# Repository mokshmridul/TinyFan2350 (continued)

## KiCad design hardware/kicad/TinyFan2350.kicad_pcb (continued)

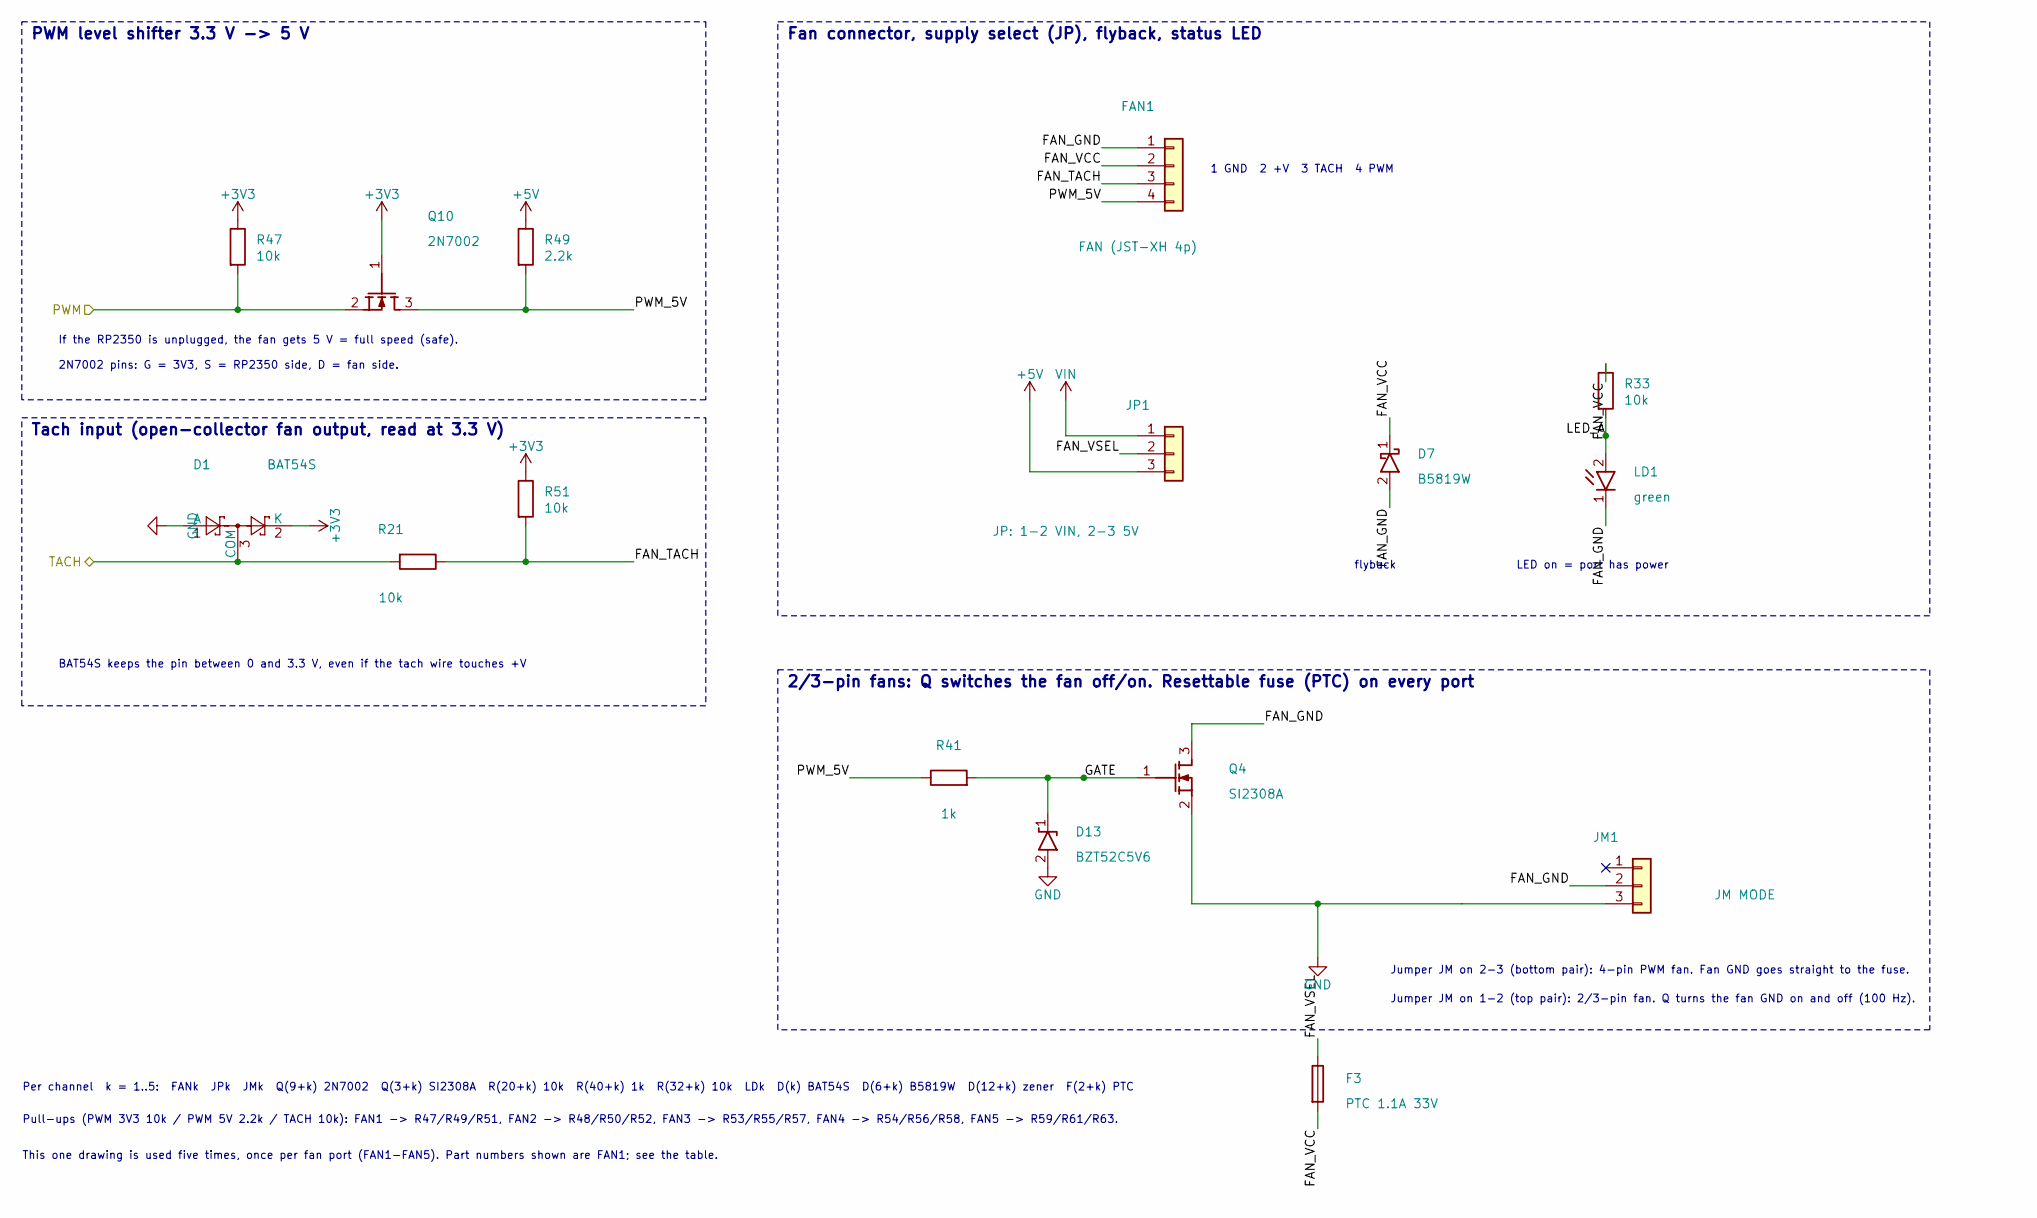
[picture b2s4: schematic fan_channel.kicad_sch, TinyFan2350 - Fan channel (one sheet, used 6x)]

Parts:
D1: BAT54S; SOT-23; MPN BAT54S-7-F; LCSC C83574
D7: B5819W; D_SOD-123; MPN B5819W; LCSC C8598
D13: BZT52C5V6; D_SOD-123; MPN BZT52C5V6; LCSC C2119
F3: PTC 1.1A 33V; Fuse_1812_4532Metric; MPN 1812L110/33GR; LCSC C7542972
FAN1: FAN (JST-XH 4p); JST_XH_B4B-XH-A_1x04_P2.50mm_Vertical; MPN B4B-XH-A(LF)(SN); LCSC C144395
JM1: JM MODE; PinHeader_1x03_P2.54mm_Vertical_TightCY; MPN 2.54-1*3P; LCSC C49257
JP1: JP: 1-2 VIN, 2-3 5V; PinHeader_1x03_P2.54mm_Vertical_TightCY; MPN 2.54-1*3P; LCSC C49257
LD1: green; LED_0805_2012Metric; MPN KT-0805G; LCSC C2297
Q4: SI2308A; SOT-23; MPN SI2308A; LCSC C347491
Q10: 2N7002; SOT-23; MPN 2N7002; LCSC C8545
R21, R33, R47, R51: 10k; R_0805_2012Metric; MPN 0805W8F1002T5E; LCSC C17414
R41: 1k; R_0805_2012Metric; MPN 0805W8F1001T5E; LCSC C17513
R49: 2.2k; R_0805_2012Metric; MPN 0805W8F2201T5E; LCSC C17520

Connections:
+3V3: D1.2 (K), Q10.1 (G), R47.1, R51.1; also elsewhere on the board
+5V: JP1.3, R49.1; also elsewhere on the board
/FAN1/FAN_GND: D7.2 (A), FAN1.1, JM1.2, LD1.1 (K), Q4.3 (D)
/FAN1/FAN_TACH: FAN1.3, R21.1, R51.2
/FAN1/FAN_VCC: D7.1 (K), F3.2, FAN1.2, R33.1
/FAN1/FAN_VSEL: F3.1, JP1.2
/FAN1/GATE: D13.1 (K), Q4.1 (G), R41.2
/FAN1/LED_A: LD1.2 (A), R33.2
/FAN1/PWM_5V: FAN1.4, Q10.3 (D), R41.1, R49.2
/FAN1_PWM: Q10.2 (S), R47.2; also elsewhere on the board
/FAN1_TACH_IO: D1.3 (COM), R21.2; also elsewhere on the board
GND: D1.1 (A), D13.2 (A), JM1.3, Q4.2 (S); also elsewhere on the board
VIN: JP1.1; also elsewhere on the board

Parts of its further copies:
D2, D3, D4, D5: BAT54S; SOT-23; MPN BAT54S-7-F; LCSC C83574
D8, D9, D10, D11: B5819W; D_SOD-123; MPN B5819W; LCSC C8598
D14, D15, D16, D17: BZT52C5V6; D_SOD-123; MPN BZT52C5V6; LCSC C2119
F4, F5, F6, F7: PTC 1.1A 33V; Fuse_1812_4532Metric; MPN 1812L110/33GR; LCSC C7542972
FAN2, FAN3, FAN4, FAN5: FAN (JST-XH 4p); JST_XH_B4B-XH-A_1x04_P2.50mm_Vertical; MPN B4B-XH-A(LF)(SN); LCSC C144395
JM2, JM3, JM4, JM5: JM MODE; PinHeader_1x03_P2.54mm_Vertical_TightCY; MPN 2.54-1*3P; LCSC C49257
JP2, JP3, JP4, JP5: JP: 1-2 VIN, 2-3 5V; PinHeader_1x03_P2.54mm_Vertical_TightCY; MPN 2.54-1*3P; LCSC C49257
LD2, LD3, LD4, LD5: green; LED_0805_2012Metric; MPN KT-0805G; LCSC C2297
Q5, Q6, Q7, Q8: SI2308A; SOT-23; MPN SI2308A; LCSC C347491
Q11, Q12, Q13, Q14: 2N7002; SOT-23; MPN 2N7002; LCSC C8545
R22, R23, R24, R25, R34, R35, R36, R37, R48, R52, R53, R54, R57, R58, R59, R63: 10k; R_0805_2012Metric; MPN 0805W8F1002T5E; LCSC C17414
R42, R43, R44, R45: 1k; R_0805_2012Metric; MPN 0805W8F1001T5E; LCSC C17513
R50, R55, R56, R61: 2.2k; R_0805_2012Metric; MPN 0805W8F2201T5E; LCSC C17520

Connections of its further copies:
+3V3: D2.2 (K), D3.2 (K), D4.2 (K), D5.2 (K), Q11.1 (G), Q12.1 (G), Q13.1 (G), Q14.1 (G), R48.1, R52.1, R53.1, R54.1, R57.1, R58.1, R59.1, R63.1; also elsewhere on the board
+5V: JP2.3, JP3.3, JP4.3, JP5.3, R50.1, R55.1, R56.1, R61.1; also elsewhere on the board
/FAN2/FAN_GND: D8.2 (A), FAN2.1, JM2.2, LD2.1 (K), Q5.3 (D)
/FAN2/FAN_TACH: FAN2.3, R22.1, R52.2
/FAN2/FAN_VCC: D8.1 (K), F4.2, FAN2.2, R34.1
/FAN2/FAN_VSEL: F4.1, JP2.2
/FAN2/GATE: D14.1 (K), Q5.1 (G), R42.2
/FAN2/LED_A: LD2.2 (A), R34.2
/FAN2/PWM_5V: FAN2.4, Q11.3 (D), R42.1, R50.2
/FAN2_PWM: Q11.2 (S), R48.2; also elsewhere on the board
/FAN2_TACH_IO: D2.3 (COM), R22.2; also elsewhere on the board
/FAN3/FAN_GND: D9.2 (A), FAN3.1, JM3.2, LD3.1 (K), Q6.3 (D)
/FAN3/FAN_TACH: FAN3.3, R23.1, R57.2
/FAN3/FAN_VCC: D9.1 (K), F5.2, FAN3.2, R35.1
/FAN3/FAN_VSEL: F5.1, JP3.2
/FAN3/GATE: D15.1 (K), Q6.1 (G), R43.2
/FAN3/LED_A: LD3.2 (A), R35.2
/FAN3/PWM_5V: FAN3.4, Q12.3 (D), R43.1, R55.2
/FAN3_PWM: Q12.2 (S), R53.2; also elsewhere on the board
/FAN3_TACH_IO: D3.3 (COM), R23.2; also elsewhere on the board
/FAN4/FAN_GND: D10.2 (A), FAN4.1, JM4.2, LD4.1 (K), Q7.3 (D)
/FAN4/FAN_TACH: FAN4.3, R24.1, R58.2
/FAN4/FAN_VCC: D10.1 (K), F6.2, FAN4.2, R36.1
/FAN4/FAN_VSEL: F6.1, JP4.2
/FAN4/GATE: D16.1 (K), Q7.1 (G), R44.2
/FAN4/LED_A: LD4.2 (A), R36.2
/FAN4/PWM_5V: FAN4.4, Q13.3 (D), R44.1, R56.2
/FAN4_PWM: Q13.2 (S), R54.2; also elsewhere on the board
/FAN4_TACH_IO: D4.3 (COM), R24.2; also elsewhere on the board
/FAN5/FAN_GND: D11.2 (A), FAN5.1, JM5.2, LD5.1 (K), Q8.3 (D)
/FAN5/FAN_TACH: FAN5.3, R25.1, R63.2
/FAN5/FAN_VCC: D11.1 (K), F7.2, FAN5.2, R37.1
/FAN5/FAN_VSEL: F7.1, JP5.2
/FAN5/GATE: D17.1 (K), Q8.1 (G), R45.2
/FAN5/LED_A: LD5.2 (A), R37.2
/FAN5/PWM_5V: FAN5.4, Q14.3 (D), R45.1, R61.2
/FAN5_PWM: Q14.2 (S), R59.2; also elsewhere on the board
/FAN5_TACH_IO: D5.3 (COM), R25.2; also elsewhere on the board
GND: D2.1 (A), D3.1 (A), D4.1 (A), D5.1 (A), D14.2 (A), D15.2 (A), D16.2 (A), D17.2 (A), JM2.3, JM3.3, JM4.3, JM5.3, Q5.2 (S), Q6.2 (S), Q7.2 (S), Q8.2 (S); also elsewhere on the board
VIN: JP2.1, JP3.1, JP4.1, JP5.1; also elsewhere on the board

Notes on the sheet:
This one drawing is used five times, once per fan port (FAN1-FAN5). Part numbers shown are FAN1; see the table.
PWM level shifter 3.3 V -> 5 V
If the RP2350 is unplugged, the fan gets 5 V = full speed (safe).
2N7002 pins: G = 3V3, S = RP2350 side, D = fan side.
Tach input (open-collector fan output, read at 3.3 V)
BAT54S keeps the pin between 0 and 3.3 V, even if the tach wire touches +V
Fan connector, supply select (JP), flyback, status LED
1 GND 2 +V 3 TACH 4 PWM
flyback
LED on = port has power
2/3-pin fans: Q switches the fan off/on. Resettable fuse (PTC) on every port
Jumper JM on 2-3 (bottom pair): 4-pin PWM fan. Fan GND goes straight to the fuse.
Jumper JM on 1-2 (top pair): 2/3-pin fan. Q turns the fan GND on and off (100 Hz).
Per channel k = 1..5: FANk JPk JMk Q(9+k) 2N7002 Q(3+k) SI2308A R(20+k) 10k R(40+k) 1k R(32+k) 10k LDk D(k) BAT54S D(6+k) B5819W D(12+k) zener F(2+k) PTC
Pull-ups (PWM 3V3 10k / PWM 5V 2.2k / TACH 10k): FAN1 -> R47/R49/R51, FAN2 -> R48/R50/R52, FAN3 -> R53/R55/R57, FAN4 -> R54/R56/R58, FAN5 -> R59/R61/R63.

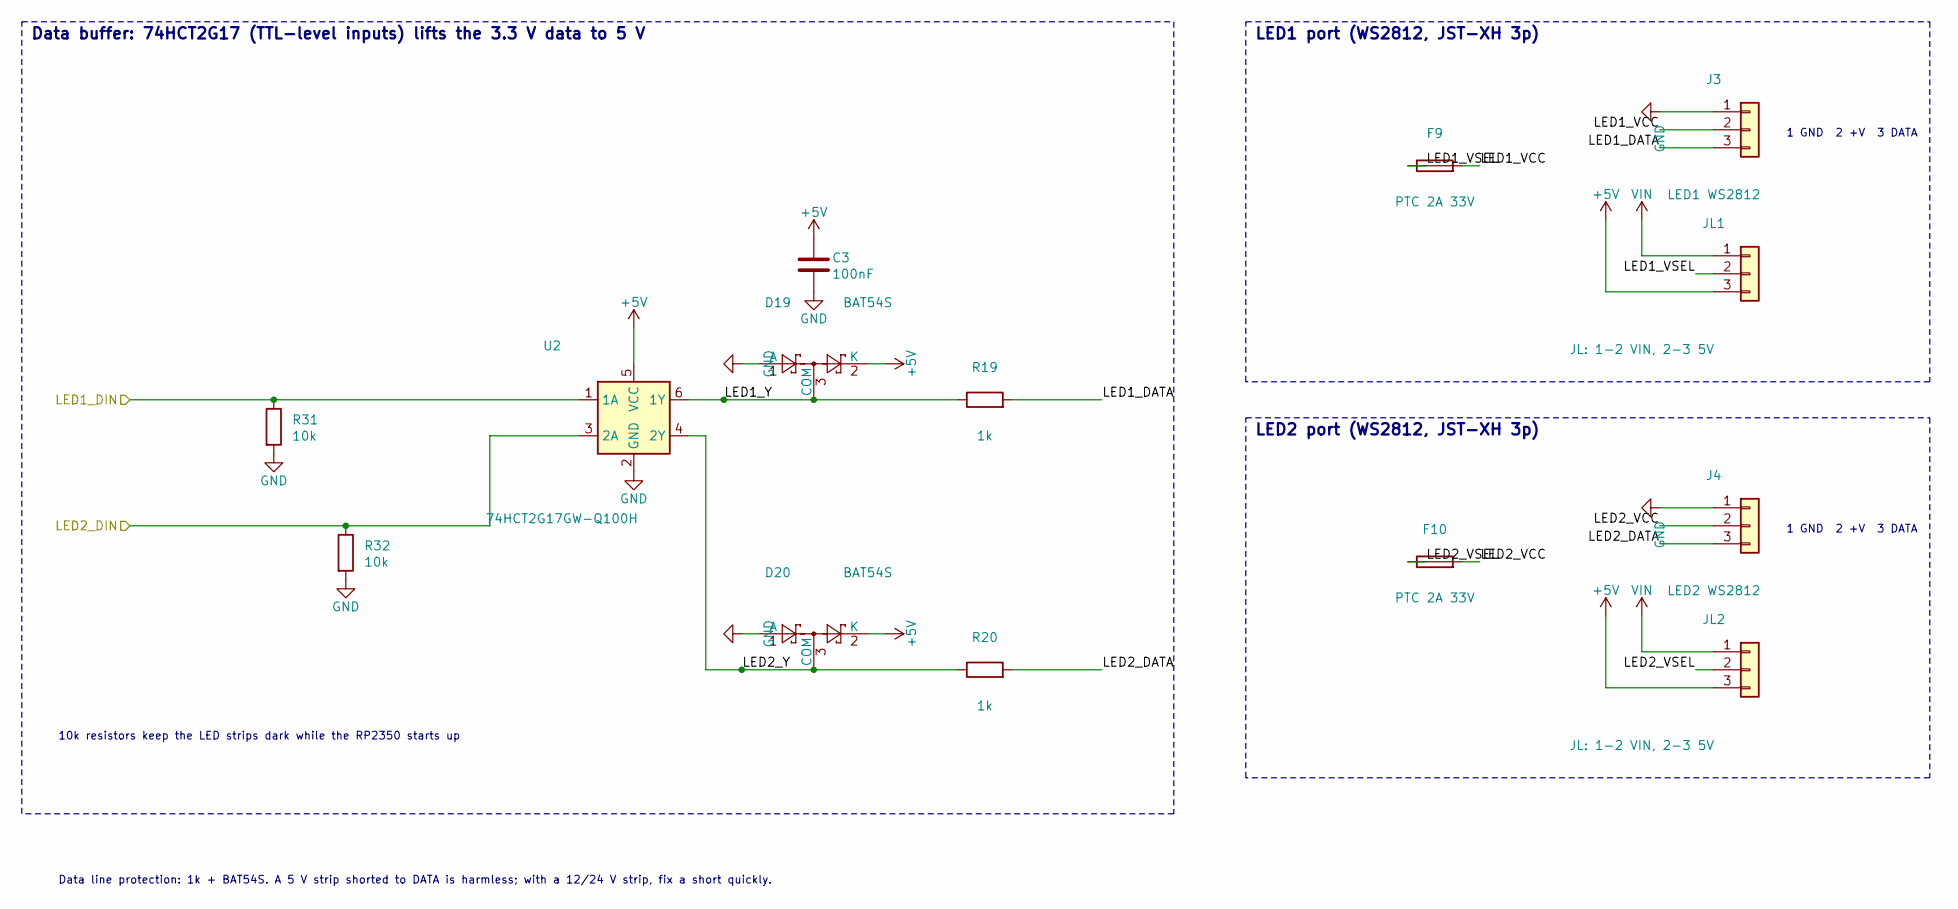
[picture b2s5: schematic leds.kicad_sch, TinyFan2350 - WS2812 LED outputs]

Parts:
C3: 100nF; C_0805_2012Metric; MPN CC0805KRX7R9BB104; LCSC C49678
D19, D20: BAT54S; SOT-23; MPN BAT54S-7-F; LCSC C83574
F9, F10: PTC 2A 33V; Fuse_1812_4532Metric; MPN 1812L200/33GR; LCSC C18198343
J3: LED1 WS2812; JST_XH_B3B-XH-A_1x03_P2.50mm_Vertical; MPN B3B-XH-A(LF)(SN); LCSC C144394
J4: LED2 WS2812; JST_XH_B3B-XH-A_1x03_P2.50mm_Vertical; MPN B3B-XH-A(LF)(SN); LCSC C144394
JL1, JL2: JL: 1-2 VIN, 2-3 5V; PinHeader_1x03_P2.54mm_Vertical_TightCY; MPN 2.54-1*3P; LCSC C49257
R19, R20: 1k; R_1206_3216Metric; MPN 1206W4F1001T5E; LCSC C4410
R31, R32: 10k; R_0805_2012Metric; MPN 0805W8F1002T5E; LCSC C17414
U2: 74HCT2G17GW-Q100H; SOT-363_SC-70-6; MPN 74HCT2G17GW-Q100H; LCSC C547569

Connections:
+5V: C3.1, D19.2 (K), D20.2 (K), JL1.3, JL2.3, U2.5 (VCC); also elsewhere on the board
/LED1_DIN: R31.1, U2.1 (1A); also elsewhere on the board
/LED2_DIN: R32.1, U2.3 (2A); also elsewhere on the board
/LEDs/LED1_DATA: J3.3, R19.2
/LEDs/LED1_VCC: F9.2, J3.2
/LEDs/LED1_VSEL: F9.1, JL1.2
/LEDs/LED1_Y: D19.3 (COM), R19.1, U2.6 (1Y)
/LEDs/LED2_DATA: J4.3, R20.2
/LEDs/LED2_VCC: F10.2, J4.2
/LEDs/LED2_VSEL: F10.1, JL2.2
/LEDs/LED2_Y: D20.3 (COM), R20.1, U2.4 (2Y)
GND: C3.2, D19.1 (A), D20.1 (A), J3.1, J4.1, R31.2, R32.2, U2.2 (GND); also elsewhere on the board
VIN: JL1.1, JL2.1; also elsewhere on the board

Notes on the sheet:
Data buffer: 74HCT2G17 (TTL-level inputs) lifts the 3.3 V data to 5 V
10k resistors keep the LED strips dark while the RP2350 starts up
LED1 port (WS2812, JST-XH 3p)
1 GND 2 +V 3 DATA
LED2 port (WS2812, JST-XH 3p)
Data line protection: 1k + BAT54S. A 5 V strip shorted to DATA is harmless; with a 12/24 V strip, fix a short quickly.

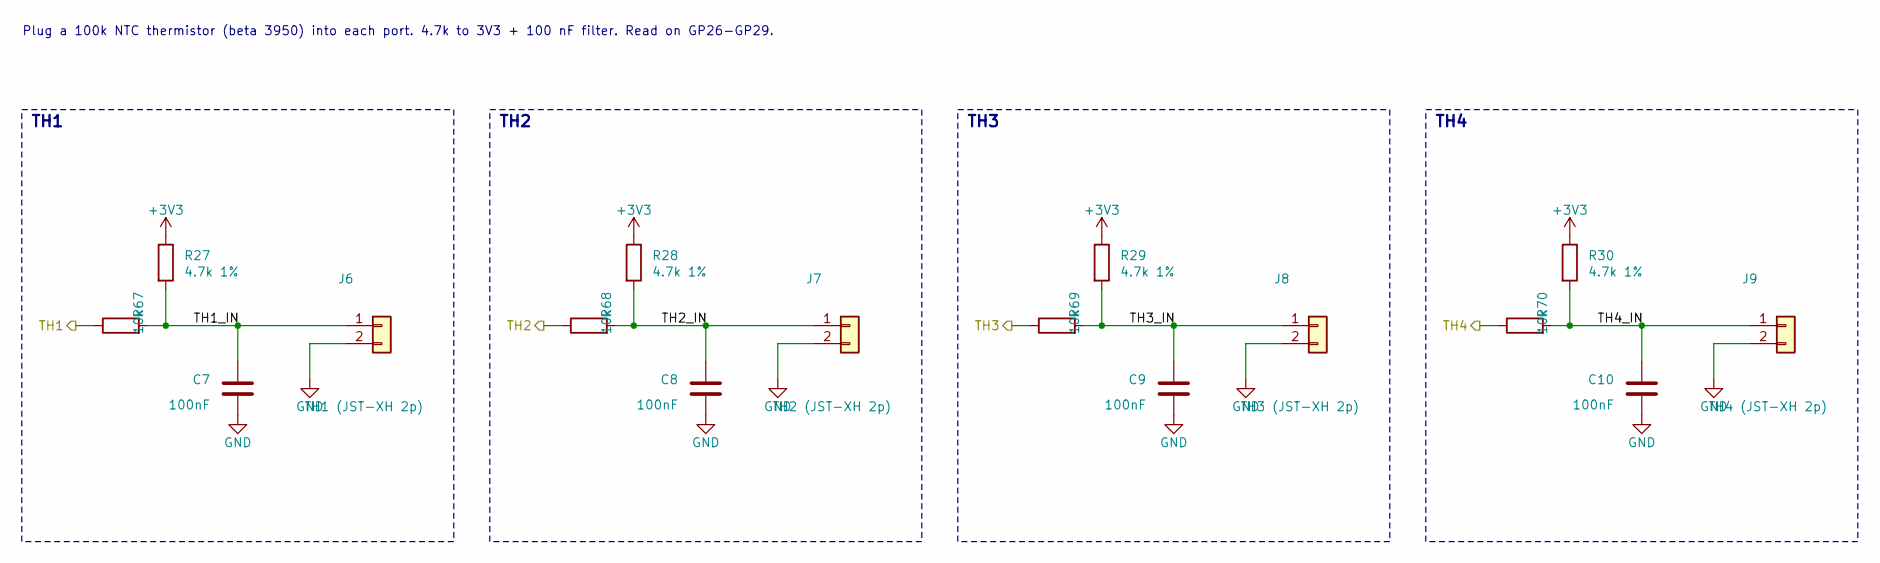
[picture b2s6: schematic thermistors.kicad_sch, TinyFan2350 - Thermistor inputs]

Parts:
C7, C8, C9, C10: 100nF; C_0805_2012Metric; MPN CC0805KRX7R9BB104; LCSC C49678
J6: TH1 (JST-XH 2p); JST_XH_B2B-XH-A_1x02_P2.50mm_Vertical; MPN B2B-XH-A(LF)(SN); LCSC C158012
J7: TH2 (JST-XH 2p); JST_XH_B2B-XH-A_1x02_P2.50mm_Vertical; MPN B2B-XH-A(LF)(SN); LCSC C158012
J8: TH3 (JST-XH 2p); JST_XH_B2B-XH-A_1x02_P2.50mm_Vertical; MPN B2B-XH-A(LF)(SN); LCSC C158012
J9: TH4 (JST-XH 2p); JST_XH_B2B-XH-A_1x02_P2.50mm_Vertical; MPN B2B-XH-A(LF)(SN); LCSC C158012
R27, R28, R29, R30: 4.7k 1%; R_1206_3216Metric; MPN 1206W4F4701T5E; LCSC C17936
R67, R68, R69, R70: 10k; R_0805_2012Metric; MPN 0805W8F1002T5E; LCSC C17414

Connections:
+3V3: R27.1, R28.1, R29.1, R30.1; also elsewhere on the board
/TH1: R67.1; also elsewhere on the board
/TH2: R68.1; also elsewhere on the board
/TH3: R69.1; also elsewhere on the board
/TH4: R70.1; also elsewhere on the board
/Thermistors/TH1_IN: C7.1, J6.1, R27.2, R67.2
/Thermistors/TH2_IN: C8.1, J7.1, R28.2, R68.2
/Thermistors/TH3_IN: C9.1, J8.1, R29.2, R69.2
/Thermistors/TH4_IN: C10.1, J9.1, R30.2, R70.2
GND: C7.2, C8.2, C9.2, C10.2, J6.2, J7.2, J8.2, J9.2; also elsewhere on the board

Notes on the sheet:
Plug a 100k NTC thermistor (beta 3950) into each port. 4.7k to 3V3 + 100 nF filter. Read on GP26-GP29.
TH1
TH2
TH3
TH4

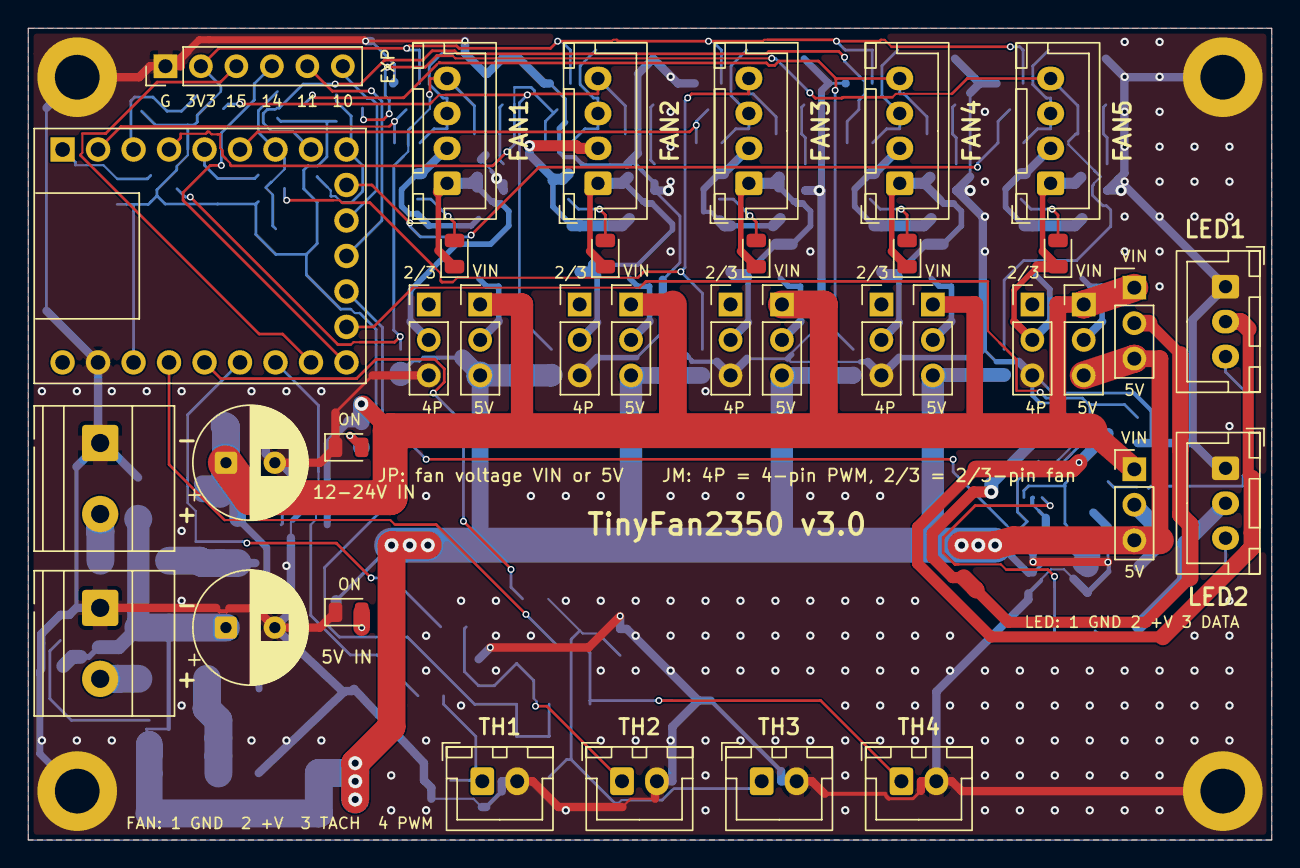
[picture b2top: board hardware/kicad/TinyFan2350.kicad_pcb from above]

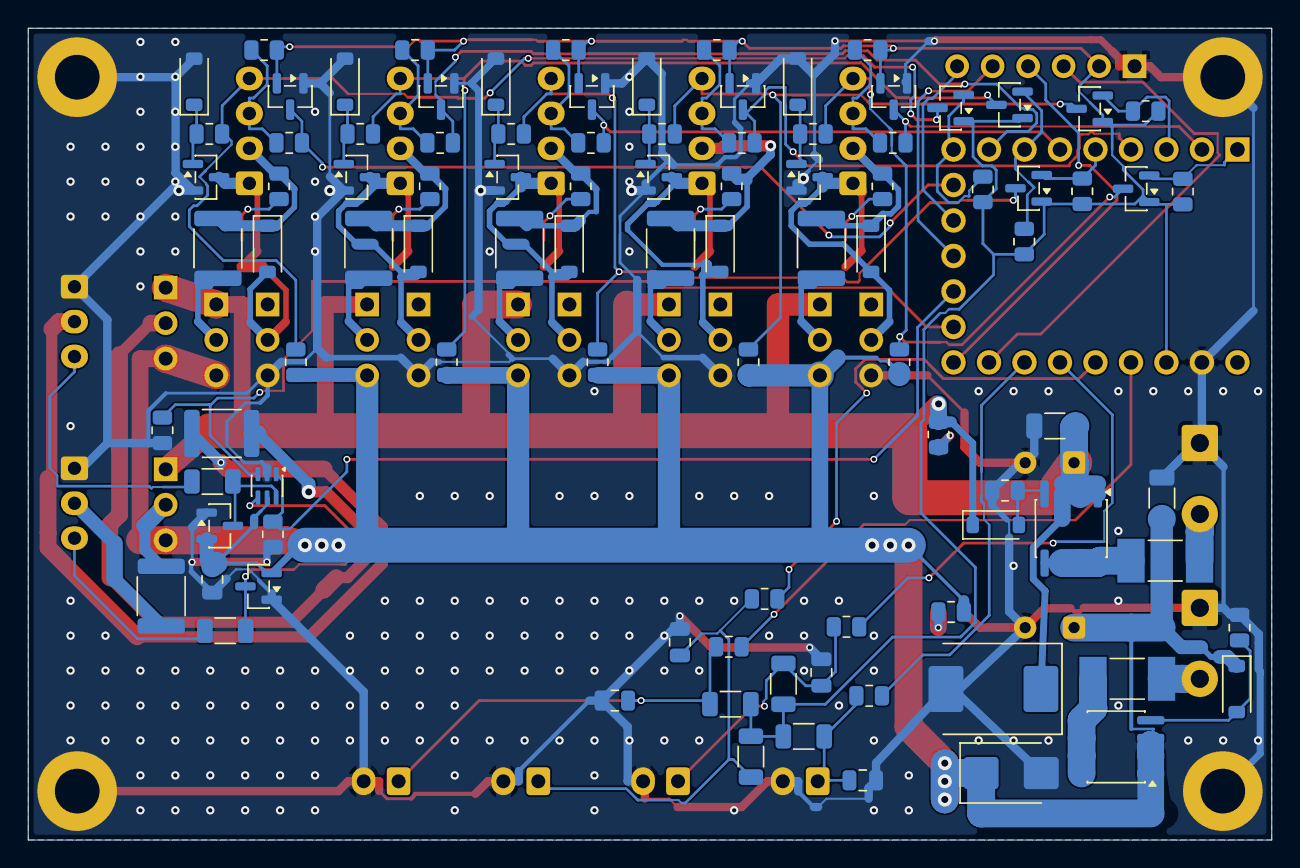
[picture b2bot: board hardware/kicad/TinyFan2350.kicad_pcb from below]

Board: 2 copper layers, 89.0 x 58.1 mm, 136 parts (96 on the bottom side), 79 nets.

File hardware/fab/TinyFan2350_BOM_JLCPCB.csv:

Comment,Designator,Footprint,LCSC Part #
10uF 50V X5R 1206,"C1,C2",C_1206_3216Metric,C13585
100nF 50V X7R 0805,"C3,C7,C8,C9,C10",C_0805_2012Metric,C49678
100uF 50V electrolytic 8x11.5,C5,CP_Radial_D8.0mm_P3.50mm_PlusLow,C88728
470uF 16V polymer 8x9,C6,CP_Radial_D8.0mm_P3.50mm_PlusLow,C2898814
BAT54S-7-F,"D1,D2,D3,D4,D5,D19,D20",SOT-23,C83574
B5819W Schottky 40V 1A,"D7,D8,D9,D10,D11",D_SOD-123,C8598
BZT52C5V6 zener 5.6V SOD-123,"D13,D14,D15,D16,D17,D23,D24",D_SOD-123,C2119
SMCJ30A TVS 30V SMC,D21,D_SMC,C408374
SMBJ5.0A TVS 5V SMB,D22,D_SMB,C260407
Littelfuse 0452005.MRL 5A slow-blow 2410,"F1,F2",Fuse_Littelfuse-NANO2-451_453,C66503
PTC 1.1A 33V 1812,"F3,F4,F5,F6,F7",Fuse_1812_4532Metric,C7542972
PTC resettable fuse 2A 33V 1812,"F9,F10",Fuse_1812_4532Metric,C18198343
B4B-XH-A,"FAN1,FAN2,FAN3,FAN4,FAN5",JST_XH_B4B-XH-A_1x04_P2.50mm_Vertical,C144395
Screw terminal 2P 5mm,"J1,J2","TerminalBlock_MKDS-1,5-2-5.08_EdgeEntry",C474881
B3B-XH-A,"J3,J4",JST_XH_B3B-XH-A_1x03_P2.50mm_Vertical,C144394
B2B-XH-A,"J6,J7,J8,J9",JST_XH_B2B-XH-A_1x02_P2.50mm_Vertical,C158012
Pin header 1x3 2.54mm,"JL1,JL2,JM1,JM2,JM3,JM4,JM5,JP1,JP2,JP3,JP4,JP5",PinHeader_1x03_P2.54mm_Vertical_TightCY,C49257
Green LED 0805,"LD1,LD2,LD3,LD4,LD5,LD7,LD8",LED_0805_2012Metric,C2297
AO4485 P-MOSFET -40V 10A SOIC-8,Q1,SOIC-8_3.9x4.9mm_P1.27mm,C51499
AO4407A P-MOSFET -30V 12A SOIC-8,Q2,SOIC-8_3.9x4.9mm_P1.27mm,C2841482
SI2308A N-MOSFET 60V 3A SOT-23,"Q4,Q5,Q6,Q7,Q8",SOT-23,C347491
2N7002 N-MOSFET 60V SOT-23,"Q10,Q11,Q12,Q13,Q14",SOT-23,C8545
1k 1% 1206,"R19,R20",R_1206_3216Metric,C4410
10k 1% 0805,"R21,R22,R23,R24,R25,R31,R32,R33,R34,R35,R36,R37,R39,R47,R48,R51,R52,R53,R54,R57,R58,R59,R63,R67,R68,R69,R70",R_0805_2012Metric,C17414
4.7k 1% 1206,"R27,R28,R29,R30",R_1206_3216Metric,C17936
1k 1% 0805,"R40,R41,R42,R43,R44,R45",R_0805_2012Metric,C17513
2.2k 0805,"R49,R50,R55,R56,R61",R_0805_2012Metric,C17520
22k 1% 0805,"R65,R66",R_0805_2012Metric,C17560
74HCT2G17GW-Q100H,U2,SOT-363_SC-70-6,C547569
